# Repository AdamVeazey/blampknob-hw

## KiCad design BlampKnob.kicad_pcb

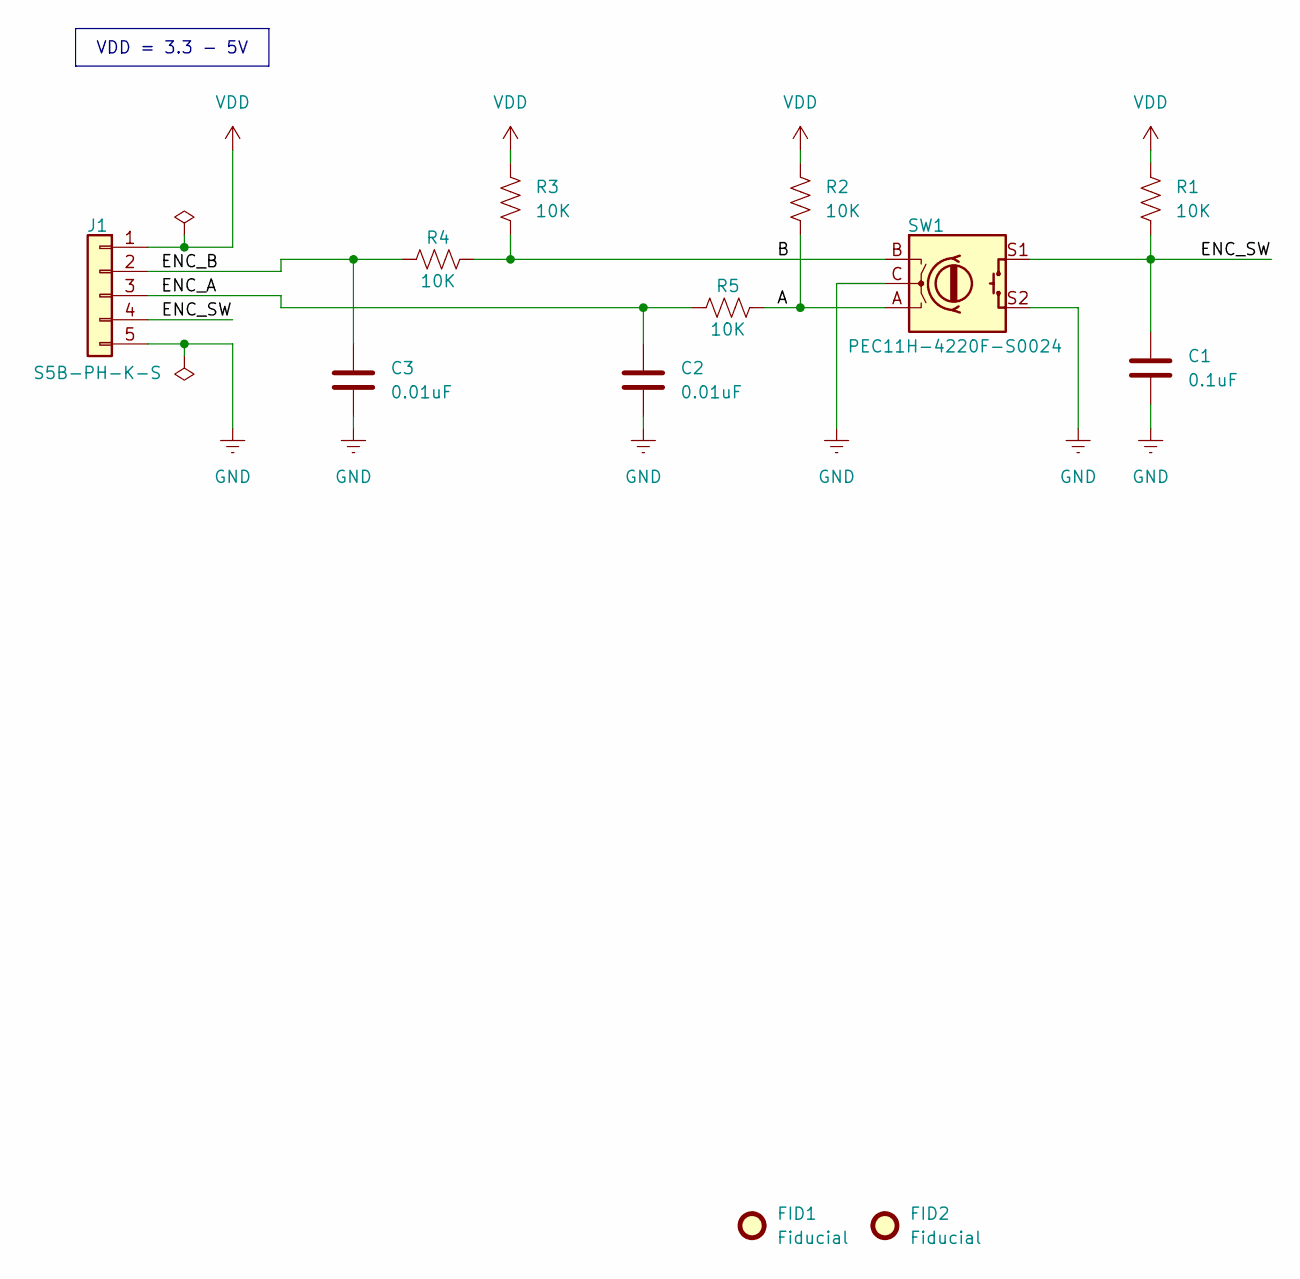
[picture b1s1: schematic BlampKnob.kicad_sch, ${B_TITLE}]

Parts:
C1: 0.1uF; C_0402_1005Metric; MFG PN CC0402KRX7R8BB104
C2, C3: 0.01uF; C_0402_1005Metric; MFG PN GRM155R71E103KA01D
FID1, FID2: Fiducial; Fiducial_0.5mm_Mask1mm
J1: S5B-PH-K-S; JST_PH_S5B-PH-K_1x05_P2.00mm_Horizontal; MFG PN S5B-PH-K-S(LF)(SN)
R1, R2, R3, R4, R5: 10K; R_0402_1005Metric; MFG PN RMCF0402FT10K0
SW1: PEC11H-4220F-S0024; SW5_PEC11H-4220F-S0024_BRN; MFG PN PEC11H-4220F-S0024

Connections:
/A: R2.2, R5.2, SW1.A
/B: R3.2, R4.2, SW1.B
/ENC_A: C2.1, J1.3, R5.1
/ENC_B: C3.1, J1.2, R4.1
/ENC_SW: C1.1, J1.4, R1.2, SW1.S1
GND: C1.2, C2.2, C3.2, J1.5, SW1.C, SW1.S2
VDD: J1.1, R1.1, R2.1, R3.1

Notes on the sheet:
VDD = 3.3 - 5V

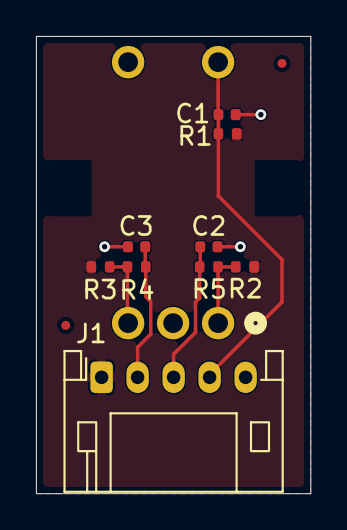
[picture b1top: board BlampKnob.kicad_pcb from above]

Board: 2 copper layers, 15.2 x 25.4 mm, 12 parts (1 on the bottom side), 7 nets.
